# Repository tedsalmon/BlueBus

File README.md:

View this project on [CADLAB.io](https://cadlab.io/project/1479).

# BlueBus

BlueBus is a Bluetooth interface module for BMW vehicles equipped with the I-Bus. It emulates a CD changer on the I-Bus to provide seamless Bluetooth audio, hands-free telephony, and comfort feature integration while maintaining full compatibility with original vehicle systems.

## Supported Vehicles

BlueBus is compatible with BMW vehicles using the I-Bus architecture:

| Platform | Models | Years |
|----------|--------|-------|
| E38 | 7 Series | 1994-2001 |
| E39 | 5 Series | 1995-2004 |
| E46 | 3 Series | 1997-2006 |
| E52 | Z8 | 2000-2003 |
| E53 | X5 | 1999-2006 |
| E83 | X3 | 2003-2010 |
| E85 | Z4 | 2003-2008 |
| E86 | Z4 | 2005-2008 |
| R50/R52/R53 | MINI | 2000-2006 |

## Features

### Bluetooth Audio
* A2DP streaming with high-quality audio output over AAC
* AVRCP metadata display (artist, title, album) on vehicle screens
* Full playback control via vehicle buttons

### Hands-Free Telephony
* HFP (Hands-Free Profile) with factory microphone integration
* Caller ID display on vehicle screen
* Answer/end calls via vehicle controls
* Telephone LED control (Red = Device Disconnected, Green = Connected)
* Voice recognition support via Siri / Google Assistant
* Emulation of OE telephone system (Minus the Menus, for now)

### Vehicle Integration
* Native DSP compatibility (analog and S/PDIF inputs)
* On-Board Computer data display (coolant temp, ambient temp, oil temp)
* GPS time synchronization for vehicles with factory Nav
* Park Distance Control integration

### Comfort Features
* Auto-lock at configurable speed threshold
* Auto-unlock on ignition off
* Comfort turn signals (Tap to signal)
* Parking lamp control

### System
* Firmware upgradable via USB
* Multi-language support (9 languages)
* Up to 8 paired Bluetooth devices

## Supported Display Units

| Unit | Description | Display |
|------|-------------|---------|
| BMBT | Board Monitor (Navigation) | Full graphical menus |
| MID | Multi-Information Display | 24-character single line |
| CD53 | Business CD Radio | 11-character single line |
| MIR | Multi-Information Radio | Single line display |

## Hardware

### Core Components
| Component | Description |
|-----------|-------------|
| PIC24FJ1024GA606 | 16-bit MCU @ 16MHz, 1MB Flash |
| BM83 | Microchip Bluetooth 5.0 Module |
| Melexis TH3122.4 | I-Bus Transceiver |

### Audio Chain
| Component | Description |
|-----------|-------------|
| PCM5122 | Line-Level DAC, 2.1V RMS, 113 dB SNR |
| DIT4096 | S/PDIF Encoder |
| PAM8406 | 5W Class-D/Class-AB Amplifier |

### Interfaces
| Component | Description |
|-----------|-------------|
| FT231XS | USB to UART (firmware updates) |

## Configuration

Settings are stored in EEPROM and can be configured through the vehicle display menus. Categories include:

* **Audio** - DAC gain, DSP input source, volume offsets
* **Telephony** - HFP mode, microphone gain, volume
* **Comfort** - Auto-lock speed, blinker count, lighting options
* **UI** - Language, temperature units, display preferences
* **Navigation** - Auto-zoom, map display mode

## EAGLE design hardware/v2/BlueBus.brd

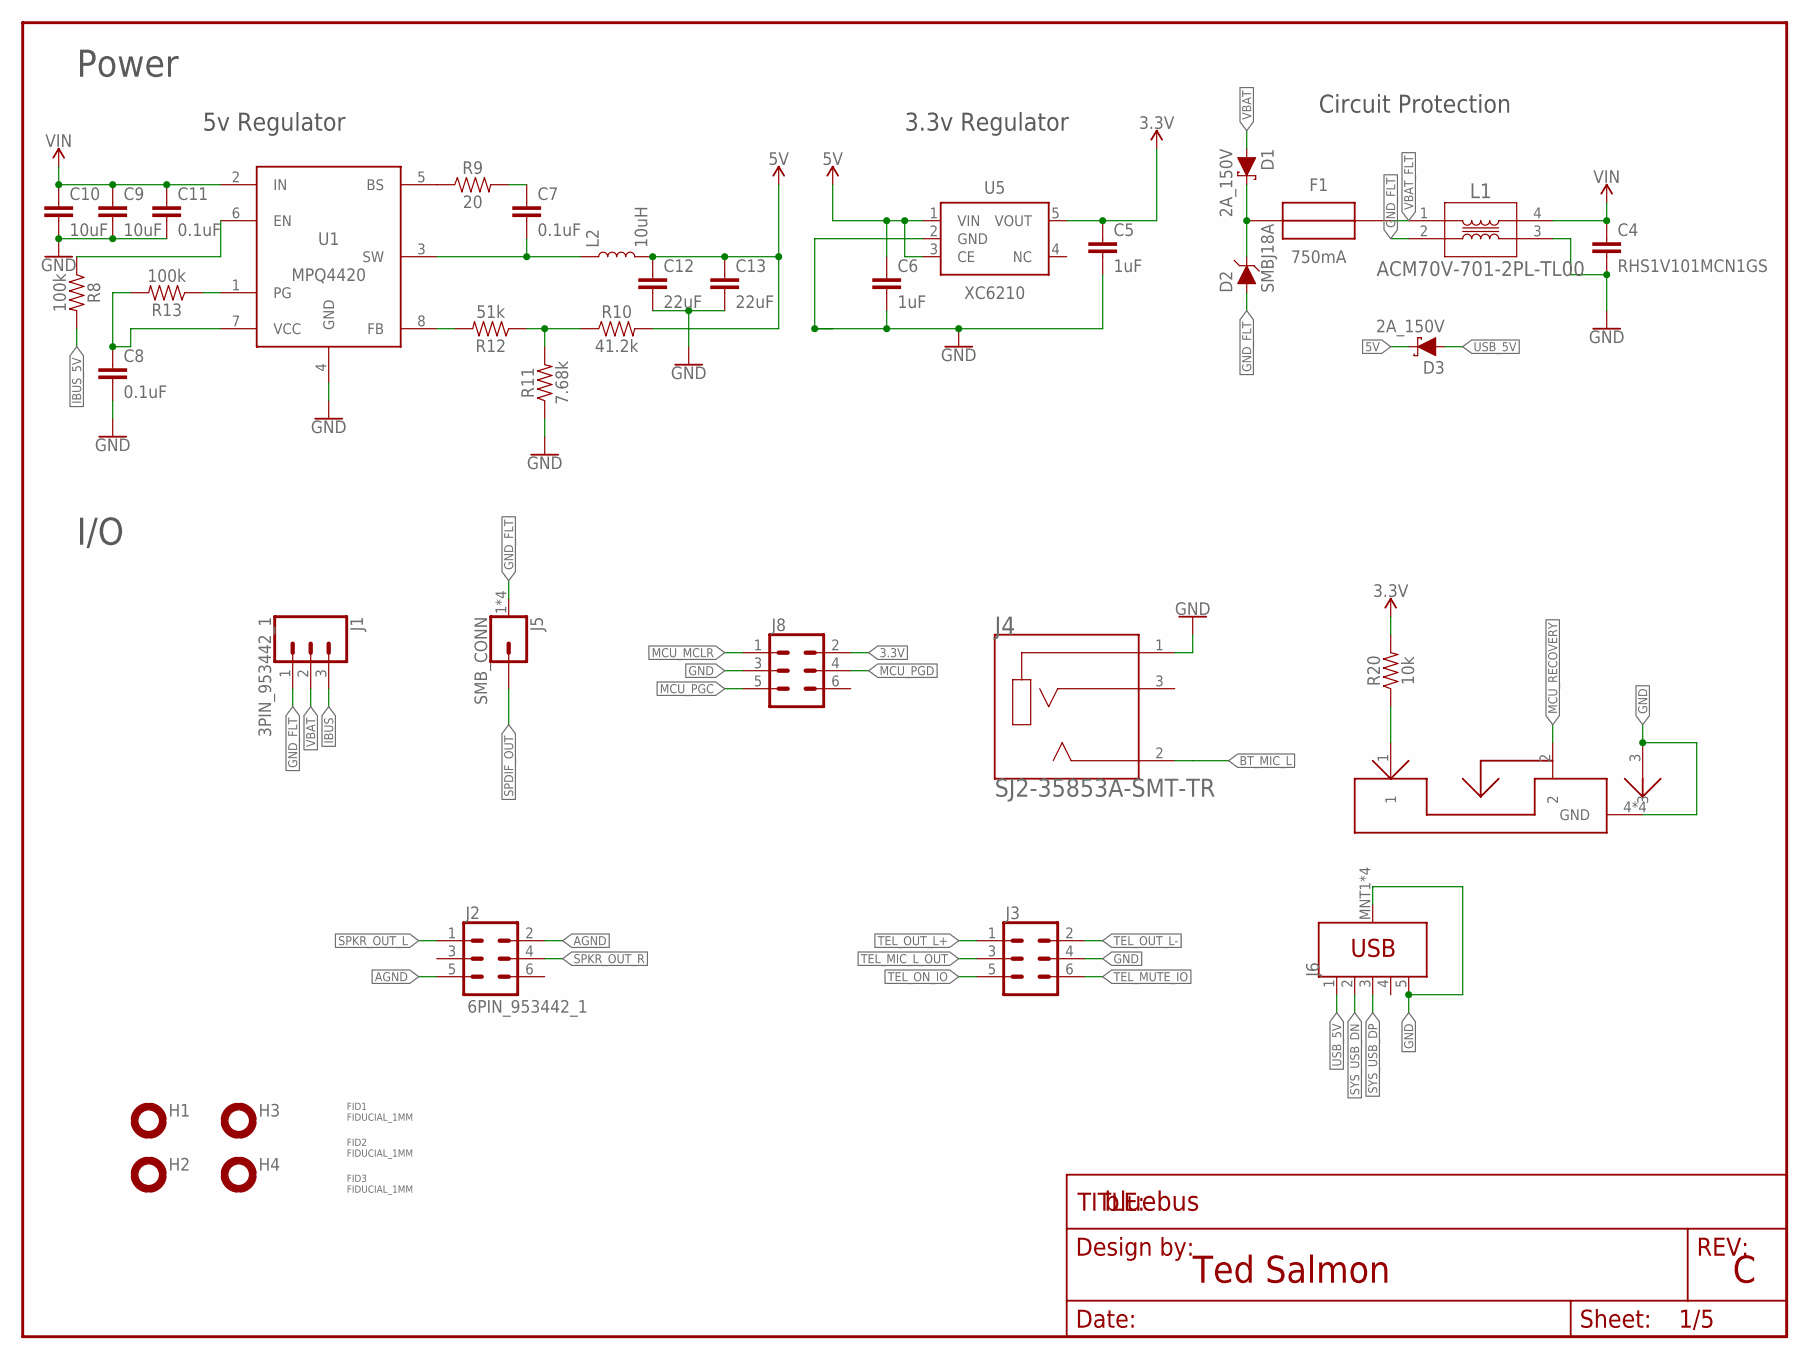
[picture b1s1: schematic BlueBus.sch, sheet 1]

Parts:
C4: RHS1V101MCN1GS
C5, C6: 1uF; 0603
C7, C8, C11: 0.1uF; 0603
C9, C10: 10uF; 1206
C12, C13: 22uF; 0805
D1, D3: 2A_150V; SOD123FL-2
D2: SMBJ18A; DO-214AA
F1: 750mA; LITTLEFUSE
FID1, FID2, FID3: FIDUCIAL_1MM
FRAME1: FRAME-LETTER; DUMMY
H1, H2, H3, H4: 2,5-HOLE; 2.5-HOLE
J1: 3PIN_953442_1; TE_MQS_3PIN
J2: 6PIN_953442_1; TE_MQS_6PIN
J3: 6PIN_5_103166_1; TE_AMPMODU_6_PIN
J4: SJ2-35853A-SMT-TR; CUI_SJ2_35853A_SMT_TR
J5: SMB_CONN; MOLEX_SMB
J6: USB3080-30-01-A
J7: PCM12SMTR
J8: TC2030NL; TC2030-NL
L1: ACM70V-701-2PL-TL00
L2: 10uH; MPL-SE5040
R8, R13: 100k; 0603
R9: 20; 0603
R10: 41.2k; 0603
R11: 7.68k; 0603
R12: 51k; 0603
R20: 10k; 0603
U1: MPQ4420; TSOT23-8
U5: XC6210; SOT23-5

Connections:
3.3V: C5.1, J8.2, R20.2, U5.5 (VOUT); also elsewhere on the board
5V: C6.1, C12.1, C13.1, D3.C, L2.2, R10.2, U5.1 (VIN), U5.3 (CE); also elsewhere on the board
5VREG_BS: R9.1, U1.5 (BS)
5VREG_BS_CAP: C7.1, R9.2
5VREG_EN: R8.1, U1.6 (EN)
5VREG_FB: R12.2, U1.8 (FB)
5VREG_FB_T: R10.1, R11.2, R12.1
5VREG_PG: R13.1, U1.1 (PG)
5VREG_SW: C7.2, L2.1, U1.3 (SW)
5VREG_VCC: C8.1, R13.2, U1.7 (VCC)
AGND: J2.2, J2.5; also elsewhere on the board
BT_MIC_L: J4.2 (TIP); also elsewhere on the board
GND: C4.2, C5.2, C6.2, C8.2, C9.2, C10.2, C11.2, C12.2, C13.2, J3.4, J4.1 (SLEEVE), J6.5 (GND), J6.MNT1 (SHIELD), J6.MNT2 (SHIELD), J6.MNT3 (SHIELD), J6.MNT4 (SHIELD), J7.3, J7.4 (GND), J7.5 (GND), J7.6 (GND), J7.7 (GND), J8.3, L1.3, R11.1, U1.4 (GND), U5.2 (GND); also elsewhere on the board
GND_FLT: D2.A, J1.1, J5.1 (GND), J5.2 (GND), J5.3 (GND), J5.4 (GND), L1.2
IBUS: J1.3; also elsewhere on the board
IBUS_5V: R8.2; also elsewhere on the board
MCU_MCLR: J8.1; also elsewhere on the board
MCU_PGC: J8.5; also elsewhere on the board
MCU_PGD: J8.4; also elsewhere on the board
MCU_RECOVERY: J7.2; also elsewhere on the board
RECOVERY_ON: J7.1, R20.1
SPDIF_OUT: J5.P$1 (1); also elsewhere on the board
SPKR_OUT_L: J2.1; also elsewhere on the board
SPKR_OUT_R: J2.4; also elsewhere on the board
SYS_USB_DN: J6.2 (D-); also elsewhere on the board
SYS_USB_DP: J6.3 (D+); also elsewhere on the board
TEL_MIC_L_OUT: J3.3; also elsewhere on the board
TEL_MUTE_IO: J3.6; also elsewhere on the board
TEL_ON_IO: J3.5; also elsewhere on the board
TEL_OUT_L+: J3.1; also elsewhere on the board
TEL_OUT_L-: J3.2; also elsewhere on the board
USB_5V: D3.A, J6.1 (VBUS)
VBAT: D1.A, J1.2
VBAT_DIODE: D1.C, D2.C, F1.IN (OUT)
VBAT_FLT: F1.OUT (IN), L1.1
VIN: C4.1, C9.1, C10.1, C11.1, L1.4, U1.2 (IN); also elsewhere on the board

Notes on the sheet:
Ted Salmon
Power
I/O
3.3v Regulator
5v Regulator
Circuit Protection

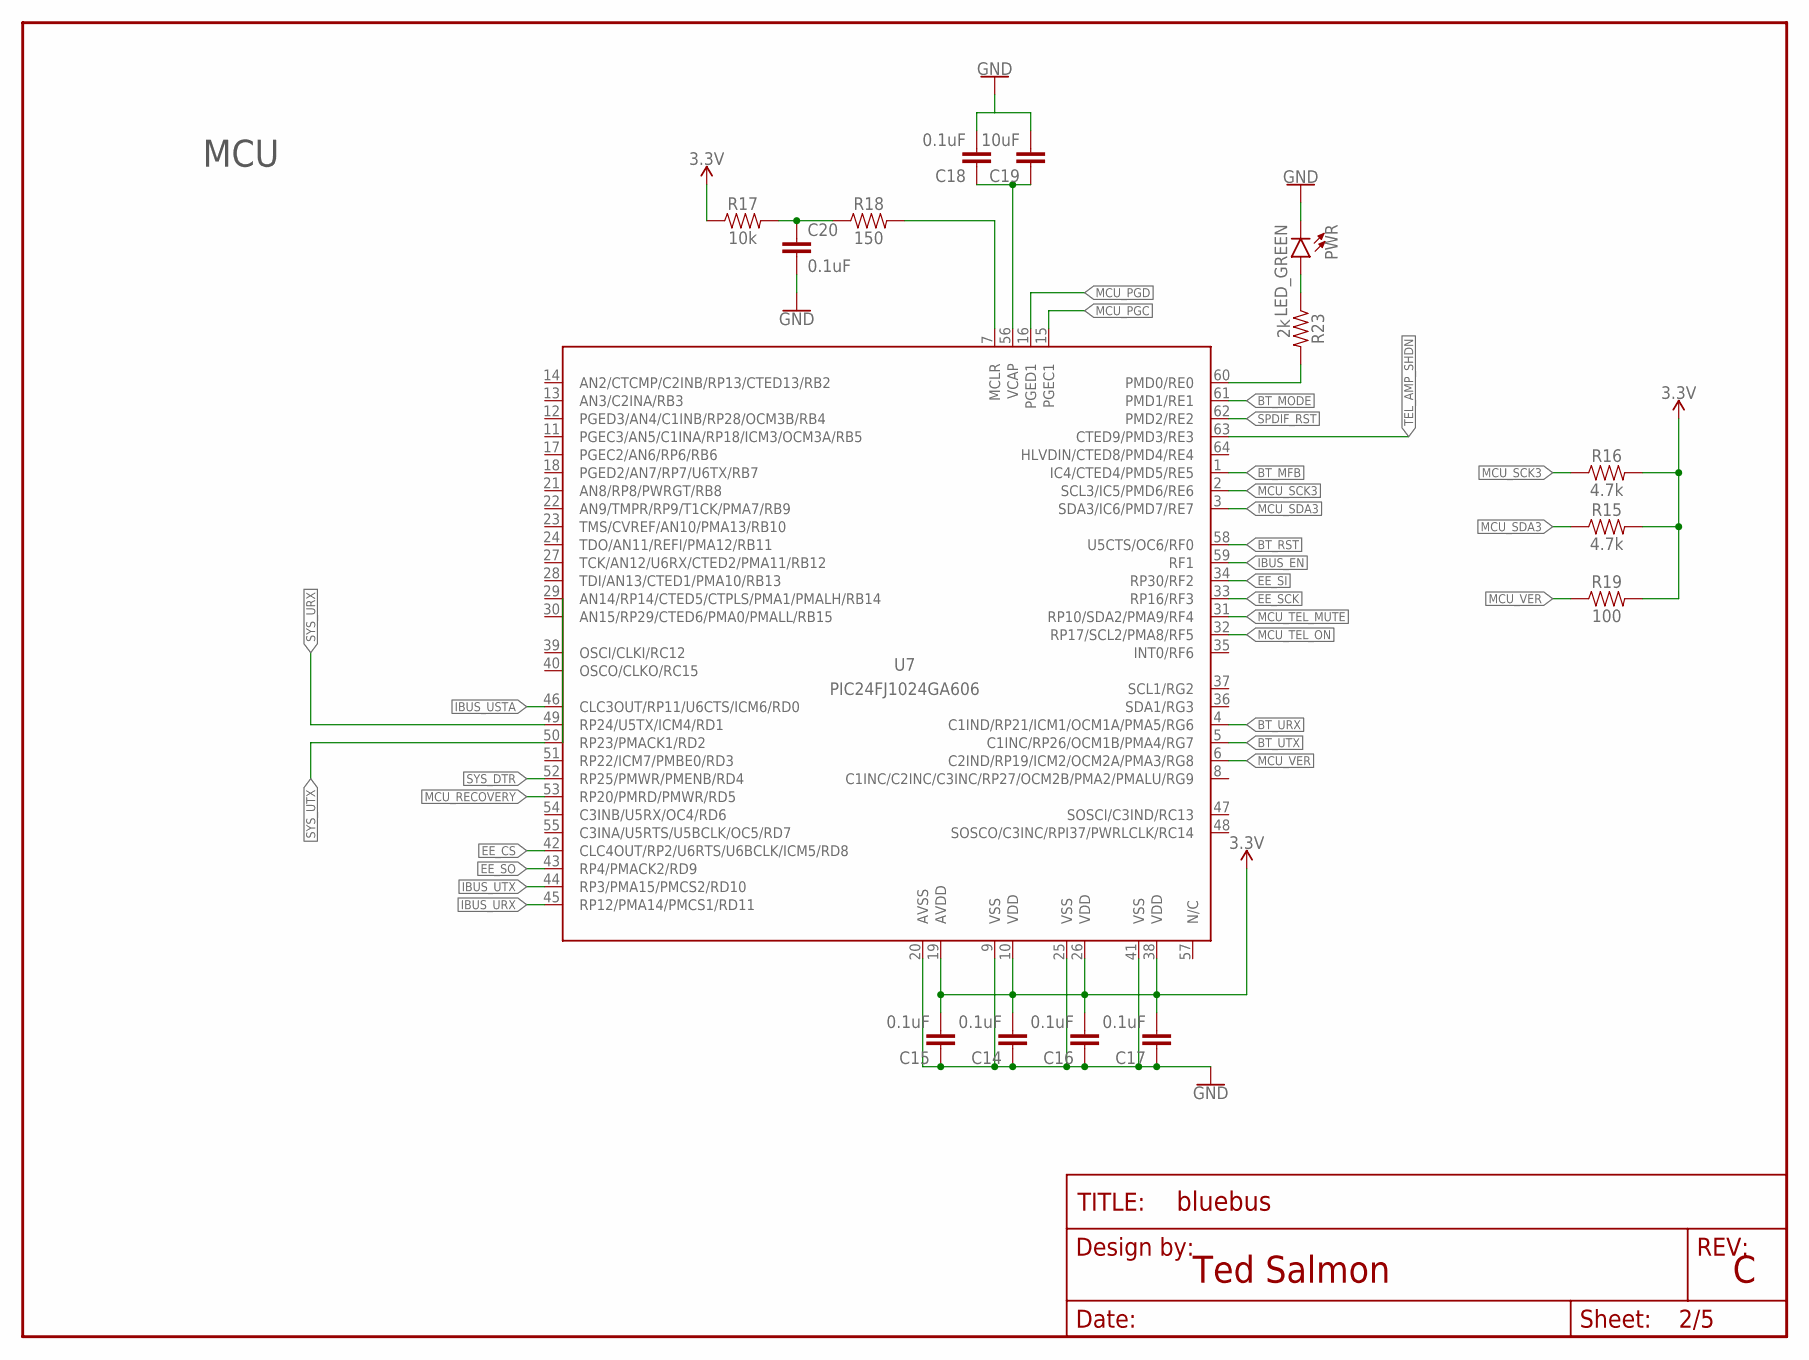
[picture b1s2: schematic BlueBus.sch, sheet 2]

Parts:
C14, C15, C16, C17, C18, C20: 0.1uF; 0603
C19: 10uF; 0603
FRAME2: FRAME-LETTER; DUMMY
PWR: LED_GREEN; LED-0805
R15, R16: 4.7k; 0603
R17: 10k; 0603
R18: 150; 0603
R19: 100; 0603
R23: 2k; 0603
U7: PIC24FJ1024GA606; TQFP64

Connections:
3.3V: C14.2, C15.2, C16.2, C17.2, R15.2, R16.2, R17.1, R19.2, U7.10 (VDD), U7.19 (AVDD), U7.26 (VDD), U7.38 (VDD); also elsewhere on the board
BT_MFB: U7.1 (IC4/CTED4/PMD5/RE5); also elsewhere on the board
BT_MODE: U7.61 (PMD1/RE1); also elsewhere on the board
BT_RST: U7.58 (U5CTS/OC6/RF0); also elsewhere on the board
BT_URX: U7.4 (C1IND/RP21/ICM1/OCM1A/PMA5/RG6); also elsewhere on the board
BT_UTX: U7.5 (C1INC/RP26/OCM1B/PMA4/RG7); also elsewhere on the board
EE_CS: U7.42 (CLC4OUT/RP2/U6RTS/U6BCLK/ICM5/RD8); also elsewhere on the board
EE_SCK: U7.33 (RP16/RF3); also elsewhere on the board
EE_SI: U7.34 (RP30/RF2); also elsewhere on the board
EE_SO: U7.43 (RP4/PMACK2/RD9); also elsewhere on the board
GND: C14.1, C15.1, C16.1, C17.1, C18.2, C19.2, C20.2, PWR.- (C), U7.9 (VSS), U7.20 (AVSS), U7.25 (VSS), U7.41 (VSS); also elsewhere on the board
IBUS_EN: U7.59 (RF1); also elsewhere on the board
IBUS_URX: U7.45 (RP12/PMA14/PMCS1/RD11); also elsewhere on the board
IBUS_USTA: U7.46 (CLC3OUT/RP11/U6CTS/ICM6/RD0); also elsewhere on the board
IBUS_UTX: U7.44 (RP3/PMA15/PMCS2/RD10); also elsewhere on the board
MCU_MCLR: R18.2, U7.7 (MCLR); also elsewhere on the board
MCU_MCLR_RES: C20.1, R17.2, R18.1
MCU_ON_LED: R23.2, U7.60 (PMD0/RE0)
MCU_ON_LED_RES: PWR.+ (A), R23.1
MCU_PGC: U7.15 (PGEC1); also elsewhere on the board
MCU_PGD: U7.16 (PGED1); also elsewhere on the board
MCU_RECOVERY: U7.53 (RP20/PMRD/PMWR/RD5); also elsewhere on the board
MCU_SCK3: R16.1, U7.2 (SCL3/IC5/PMD6/RE6); also elsewhere on the board
MCU_SDA3: R15.1, U7.3 (SDA3/IC6/PMD7/RE7); also elsewhere on the board
MCU_TEL_MUTE: U7.31 (RP10/SDA2/PMA9/RF4); also elsewhere on the board
MCU_TEL_ON: U7.32 (RP17/SCL2/PMA8/RF5); also elsewhere on the board
MCU_VCAP: C18.1, C19.1, U7.56 (VCAP)
MCU_VER: R19.1, U7.6 (C2IND/RP19/ICM2/OCM2A/PMA3/RG8)
SPDIF_RST: U7.62 (PMD2/RE2); also elsewhere on the board
SYS_DTR: U7.52 (RP25/PMWR/PMENB/RD4); also elsewhere on the board
SYS_URX: U7.49 (RP24/U5TX/ICM4/RD1); also elsewhere on the board
SYS_UTX: U7.50 (RP23/PMACK1/RD2); also elsewhere on the board
TEL_AMP_SHDN: U7.63 (CTED9/PMD3/RE3); also elsewhere on the board

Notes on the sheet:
Ted Salmon
MCU

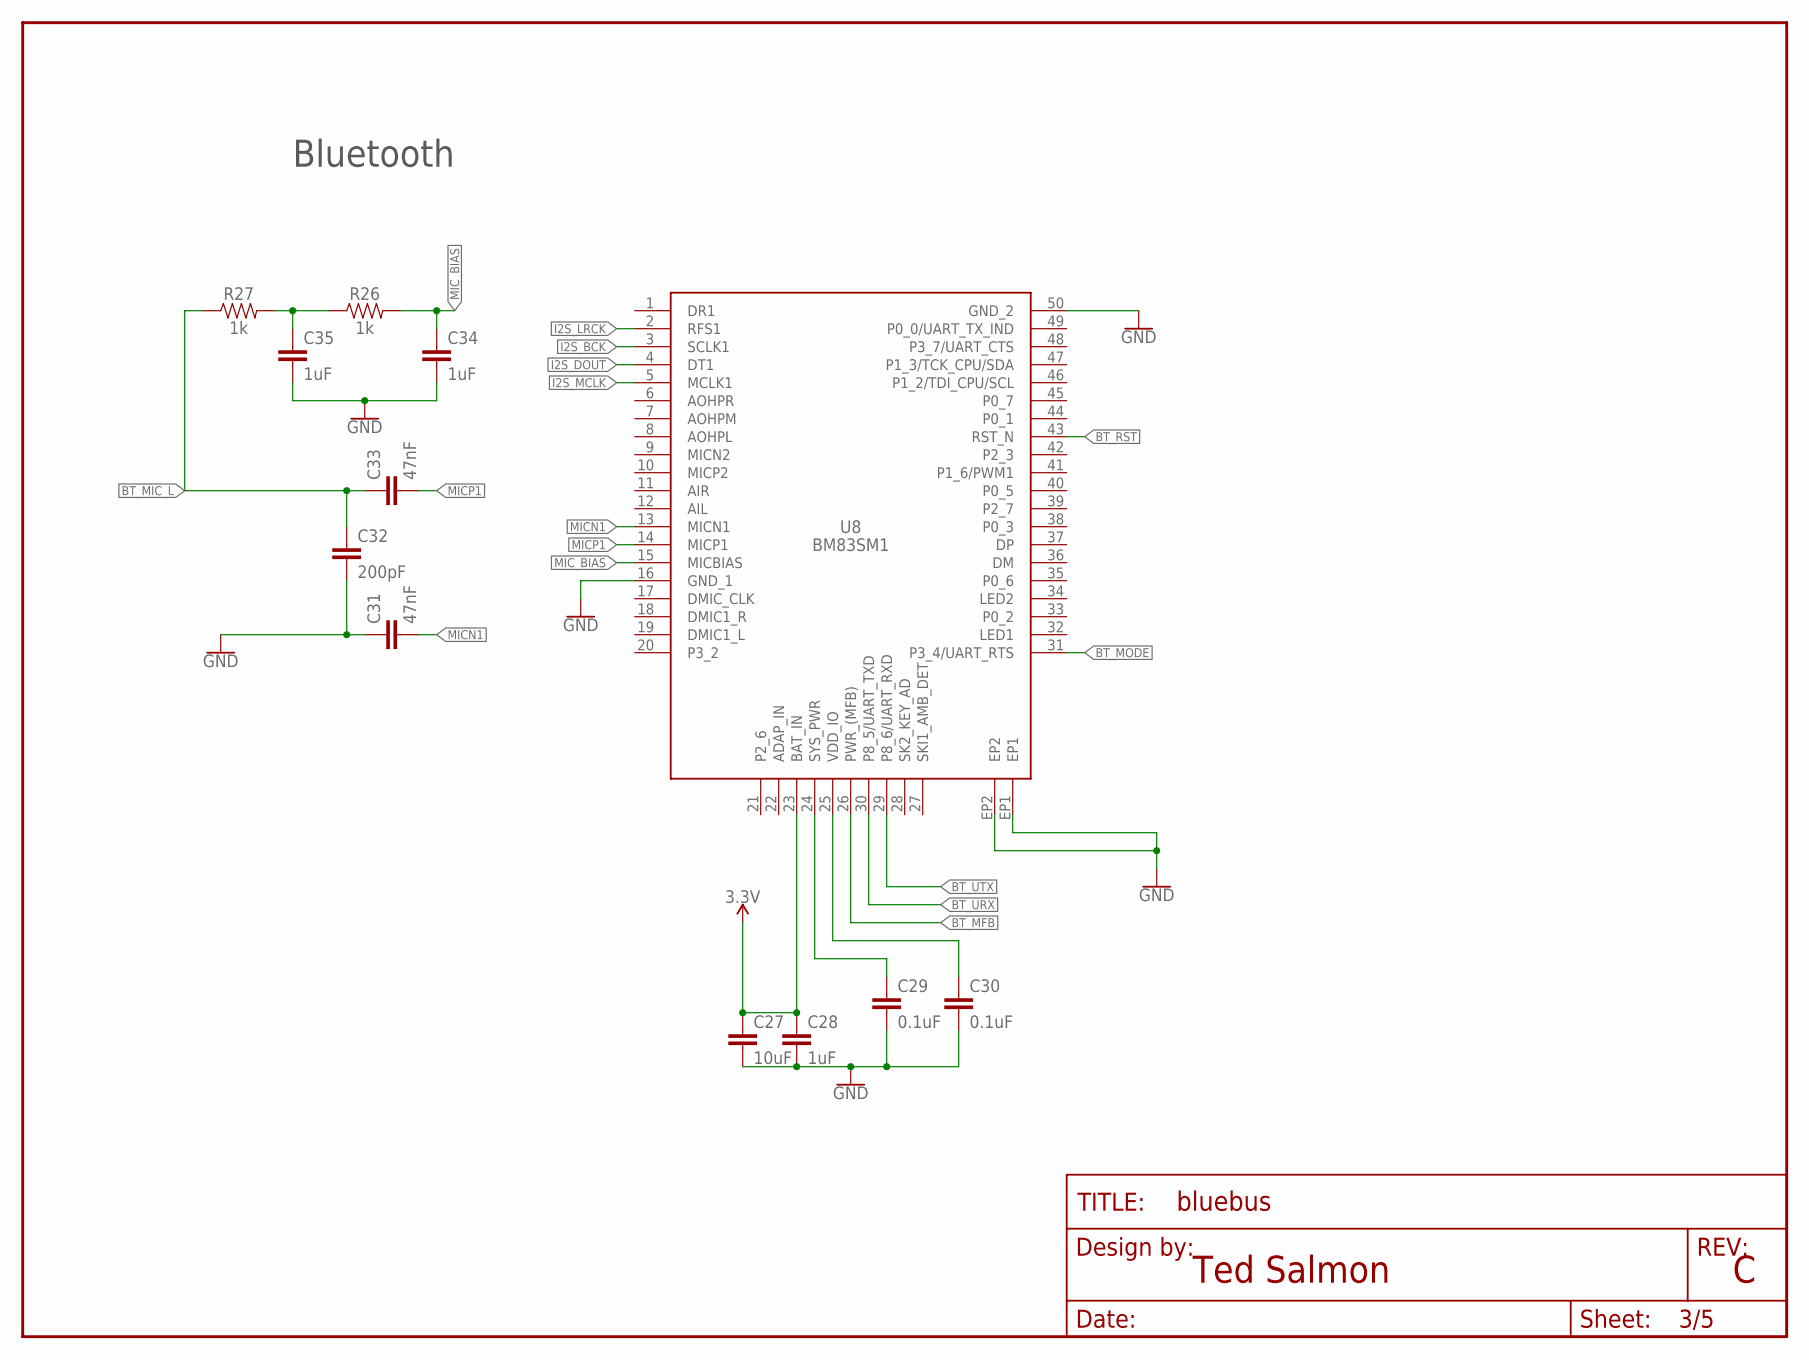
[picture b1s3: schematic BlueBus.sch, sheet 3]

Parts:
C27: 10uF; 0603
C28, C34, C35: 1uF; 0603
C29, C30: 0.1uF; 0603
C31, C33: 47nF; 0603
C32: 200pF; 0603
FRAME4: FRAME-LETTER; DUMMY
R26, R27: 1k; 0603
U8: BM83SM1

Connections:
3.3V: C27.1, C28.1, U8.23 (BAT_IN); also elsewhere on the board
BT_MFB: U8.26 (PWR_(MFB)); also elsewhere on the board
BT_MIC_L: C32.1, C33.1, R27.1; also elsewhere on the board
BT_MODE: U8.31 (P3_4/UART_RTS); also elsewhere on the board
BT_RST: U8.43 (RST_N); also elsewhere on the board
BT_SYS_PWR: C29.1, U8.24 (SYS_PWR)
BT_URX: U8.30 (P8_5/UART_TXD); also elsewhere on the board
BT_UTX: U8.29 (P8_6/UART_RXD); also elsewhere on the board
BT_VDD_IO: C30.1, U8.25 (VDD_IO)
GND: C27.2, C28.2, C29.2, C30.2, C31.1, C32.2, C34.2, C35.2, U8.16 (GND_1), U8.50 (GND_2), U8.EP1, U8.EP2; also elsewhere on the board
I2S_BCK: U8.3 (SCLK1); also elsewhere on the board
I2S_DOUT: U8.4 (DT1); also elsewhere on the board
I2S_LRCK: U8.2 (RFS1); also elsewhere on the board
I2S_MCLK: U8.5 (MCLK1); also elsewhere on the board
MICN1: C31.2, U8.13 (MICN1)
MICP1: C33.2, U8.14 (MICP1)
MICP1_RES: C35.1, R26.1, R27.2
MIC_BIAS: C34.1, R26.2, U8.15 (MICBIAS)

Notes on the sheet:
Bluetooth
Ted Salmon

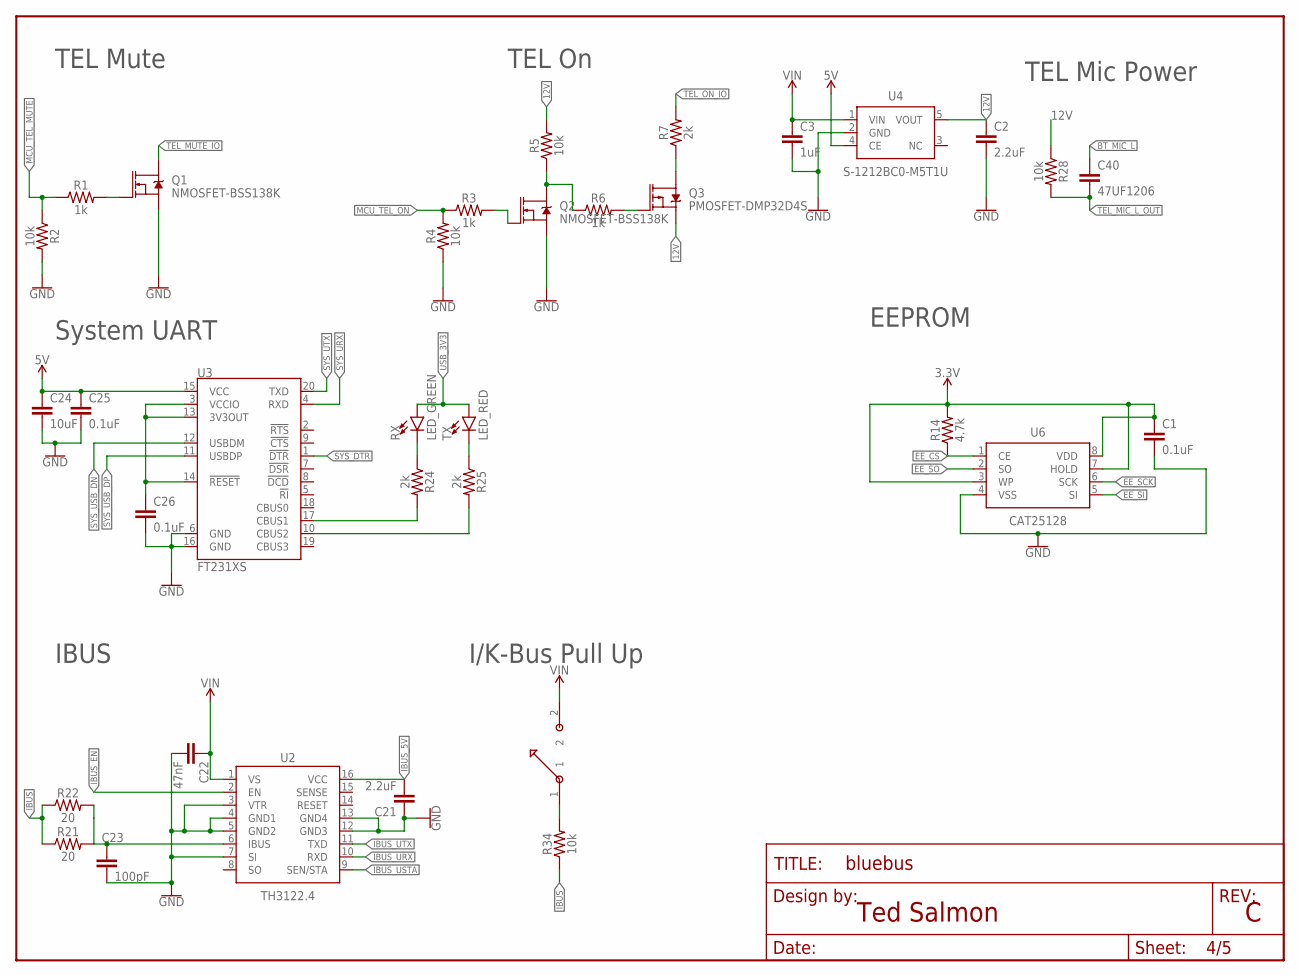
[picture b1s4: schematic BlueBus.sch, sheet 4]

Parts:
C1, C25, C26: 0.1uF; 0603
C2, C21: 2.2uF; 0603
C3: 1uF; 0603
C22: 47nF; 0603
C23: 100pF; 0603
C24: 10uF; 0603
C40: 47UF1206; 1206
FRAME3: FRAME-LETTER; DUMMY
Q1, Q2: NMOSFET-BSS138K; SOT-23
Q3: PMOSFET-DMP32D4S; SOT-23
R1, R3, R6: 1k; 0603
R2, R4, R5, R28, R34: 10k; 0603
R7, R24, R25: 2k; 0603
R14: 4.7k; 0603
R21, R22: 20; 0603
RX: LED_GREEN; LED-0805
SW1: CHS-01TA1
TX: LED_RED; LED-0805
U2: TH3122.4; SOIC16DF
U3: FT231XS; SSOP20_L
U4: S-1212BC0-M5T1U; SOT23-5
U6: CAT25128; TSSOP-8

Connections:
3.3V: C1.1, R14.2, U6.3 (WP), U6.7 (HOLD), U6.8 (VDD); also elsewhere on the board
5V: C24.1, C25.1, U3.15 (VCC), U4.4 (CE); also elsewhere on the board
12V: C2.1, Q3.2 (S), R5.2, R28.1, U4.5 (VOUT)
BT_MIC_L: C40.1; also elsewhere on the board
EE_CS: R14.1, U6.1 (CE); also elsewhere on the board
EE_SCK: U6.6 (SCK); also elsewhere on the board
EE_SI: U6.5 (SI); also elsewhere on the board
EE_SO: U6.2 (SO); also elsewhere on the board
GND: C1.2, C2.2, C3.2, C21.1, C22.2, C23.2, C24.2, C25.2, C26.2, Q1.2 (S), Q2.2 (S), R2.2, R4.1, U2.3 (VTR), U2.4 (GND1), U2.5 (GND2), U2.7 (SI), U2.12 (GND3), U2.13 (GND4), U3.6 (GND), U3.16 (GND), U4.2 (GND), U6.4 (VSS); also elsewhere on the board
IBUS: R21.1, R22.1, R34.1; also elsewhere on the board
IBUS_5V: C21.2, U2.16 (VCC); also elsewhere on the board
IBUS_EN: U2.2 (EN); also elsewhere on the board
IBUS_FILT: C23.1, R21.2, R22.2, U2.6 (IBUS)
IBUS_PU: R34.2, SW1.1
IBUS_URX: U2.10 (RXD); also elsewhere on the board
IBUS_USTA: U2.9 (SEN/STA); also elsewhere on the board
IBUS_UTX: U2.11 (TXD); also elsewhere on the board
MCU_TEL_MUTE: R1.1, R2.1; also elsewhere on the board
MCU_TEL_MUTE_RES: Q1.1 (G), R1.2
MCU_TEL_ON: R3.1, R4.2; also elsewhere on the board
MCU_TEL_ON_NRES: Q2.1 (G), R3.2
SYS_DTR: U3.1 (!DTR); also elsewhere on the board
SYS_RX_LED: R24.2, U3.17 (CBUS1)
SYS_RX_LED_RES: R24.1, RX.- (C)
SYS_TX_LED: R25.2, U3.10 (CBUS2)
SYS_TX_LED_RES: R25.1, TX.- (C)
SYS_URX: U3.4 (RXD); also elsewhere on the board
SYS_USB_DN: U3.12 (USBDM); also elsewhere on the board
SYS_USB_DP: U3.11 (USBDP); also elsewhere on the board
SYS_UTX: U3.20 (TXD); also elsewhere on the board
TEL_MIC_L_OUT: C40.2, R28.2; also elsewhere on the board
TEL_MUTE_IO: Q1.3 (D); also elsewhere on the board
TEL_ON: Q3.3 (D), R7.1
TEL_ON_IO: R7.2; also elsewhere on the board
TEL_ON_P: Q2.3 (D), R5.1, R6.1
TEL_ON_P_RES: Q3.1 (G), R6.2
USB_3V3: C26.1, RX.+ (A), TX.+ (A), U3.3 (VCCIO), U3.13 (3V3OUT), U3.14 (!RESET)
VIN: C3.1, C22.1, SW1.2, U2.1 (VS), U4.1 (VIN); also elsewhere on the board

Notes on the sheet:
Ted Salmon
IBUS
EEPROM
TEL On
TEL Mute
TEL Mic Power
System UART
I/K-Bus Pull Up

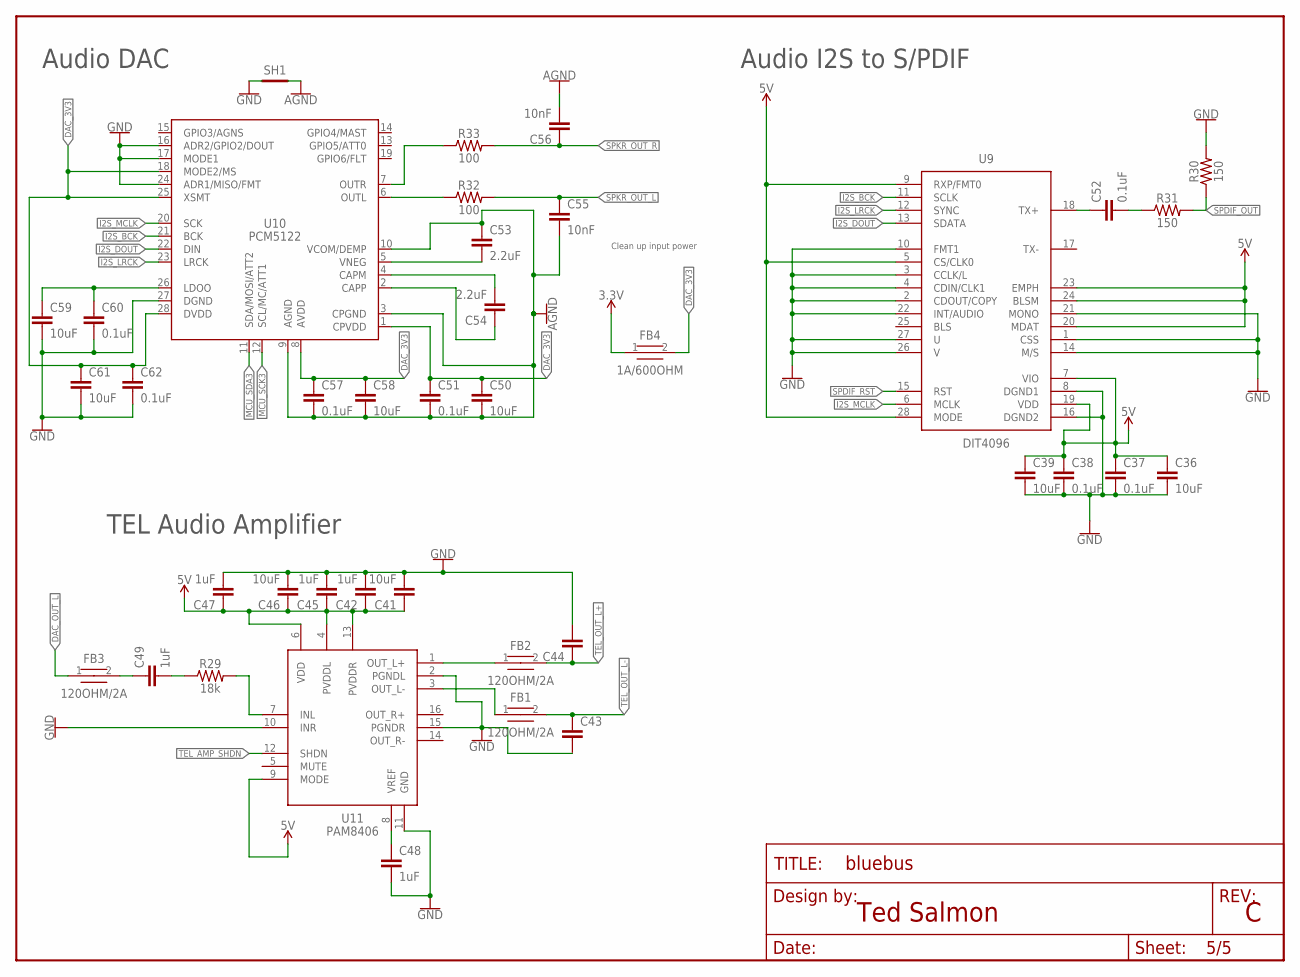
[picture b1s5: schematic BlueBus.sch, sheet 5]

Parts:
C36, C39, C41, C46, C50, C58, C59, C61: 10uF; 0603
C37, C38, C51, C52, C57, C60, C62: 0.1uF; 0603
C42, C45, C47, C48, C49: 1uF; 0603
C43, C44: 200pF; 0603
C53, C54: 2.2uF; 0603
C55, C56: 10nF; 0603
FB1, FB2, FB3: 120OHM/2A; 0603
FB4: 1A/600OHM; 0603
FRAME5: FRAME-LETTER; DUMMY
R29: 18k; 0603
R30, R31: 150; 0603
R32, R33: 100; 0603
SH1: SHORTT5; SHORT_TOP-50
U9: DIT4096; TSSOP28
U10: PCM5122; TSSOP28
U11: PAM8406; SOP-16

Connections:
3.3V: FB4.1; also elsewhere on the board
5V: C36.1, C37.1, C38.1, C39.1, C41.1, C42.1, C45.1, C46.1, C47.1, U9.5 (CS/CLK0), U9.7 (VIO), U9.9 (RXP/FMT0), U9.19 (VDD), U9.20 (MDAT), U9.23 (EMPH), U9.24 (BLSM), U9.28 (MODE), U11.4 (PVDDL), U11.6 (VDD), U11.9 (MODE), U11.13 (PVDDR); also elsewhere on the board
AGND: C50.2, C51.2, C53.1, C55.2, C56.2, C57.2, C58.2, SH1.2, U10.3 (CPGND), U10.9 (AGND), U10.10 (VCOM/DEMP); also elsewhere on the board
DAC_3V3: C50.1, C51.1, C57.1, C58.1, C61.1, C62.1, FB4.2, U10.1 (CPVDD), U10.8 (AVDD), U10.18 (MODE2/MS), U10.25 (XSMT), U10.28 (DVDD)
DAC_CAPM: C54.2, U10.4 (CAPM)
DAC_CAPP: C54.1, U10.2 (CAPP)
DAC_LDOO: C59.1, C60.1, U10.26 (LDOO)
DAC_OUT_L: FB3.1, R32.1, U10.6 (OUTL)
DAC_OUT_R: R33.1, U10.7 (OUTR)
DAC_VNEG: C53.2, U10.5 (VNEG)
GND: C36.2, C37.2, C38.2, C39.2, C41.2, C42.2, C43.2, C44.2, C45.2, C46.2, C47.2, C48.2, C59.2, C60.2, C61.2, C62.2, R30.2, SH1.1, U9.1 (CSS), U9.2 (CDOUT/COPY), U9.3 (CCLK/L), U9.4 (CDIN/CLK1), U9.8 (DGND1), U9.10 (FMT1), U9.14 (M/S), U9.16 (DGND2), U9.21 (MONO), U9.22 (INT/AUDIO), U9.26 (V), U9.27 (U), U10.16 (ADR2/GPIO2/DOUT), U10.17 (MODE1), U10.24 (ADR1/MISO/FMT), U10.27 (DGND), U11.2 (PGNDL), U11.10 (INR), U11.11 (GND), U11.15 (PGNDR); also elsewhere on the board
I2S_BCK: U9.11 (SCLK), U10.21 (BCK); also elsewhere on the board
I2S_DOUT: U9.13 (SDATA), U10.22 (DIN); also elsewhere on the board
I2S_LRCK: U9.12 (SYNC), U10.23 (LRCK); also elsewhere on the board
I2S_MCLK: U9.6 (MCLK), U10.20 (SCK); also elsewhere on the board
MCU_SCK3: U10.12 (SCL/MC/ATT1); also elsewhere on the board
MCU_SDA3: U10.11 (SDA/MOSI/ATT2); also elsewhere on the board
SPDIF_OUT: R30.1, R31.2; also elsewhere on the board
SPDIF_RST: U9.15 (RST); also elsewhere on the board
SPDIF_TX_FLT: C52.1, U9.18 (TX+)
SPDIF_TX_RES: C52.2, R31.1
SPKR_OUT_L: C55.1, R32.2; also elsewhere on the board
SPKR_OUT_R: C56.1, R33.2; also elsewhere on the board
TEL_AMP_IN: C49.1, FB3.2
TEL_AMP_INL: R29.2, U11.7 (INL)
TEL_AMP_INL_CAP_RES: C49.2, R29.1
TEL_AMP_OUT_L+: FB2.1, U11.1 (OUT_L+)
TEL_AMP_OUT_L-: FB1.1, U11.3 (OUT_L-)
TEL_AMP_SHDN: U11.12 (SHDN); also elsewhere on the board
TEL_AMP_VREF: C48.1, U11.8 (VREF)
TEL_OUT_L+: C44.1, FB2.2; also elsewhere on the board
TEL_OUT_L-: C43.1, FB1.2; also elsewhere on the board

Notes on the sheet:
Audio DAC
Audio I2S to S/PDIF
TEL Audio Amplifier
Ted Salmon
Clean up input power

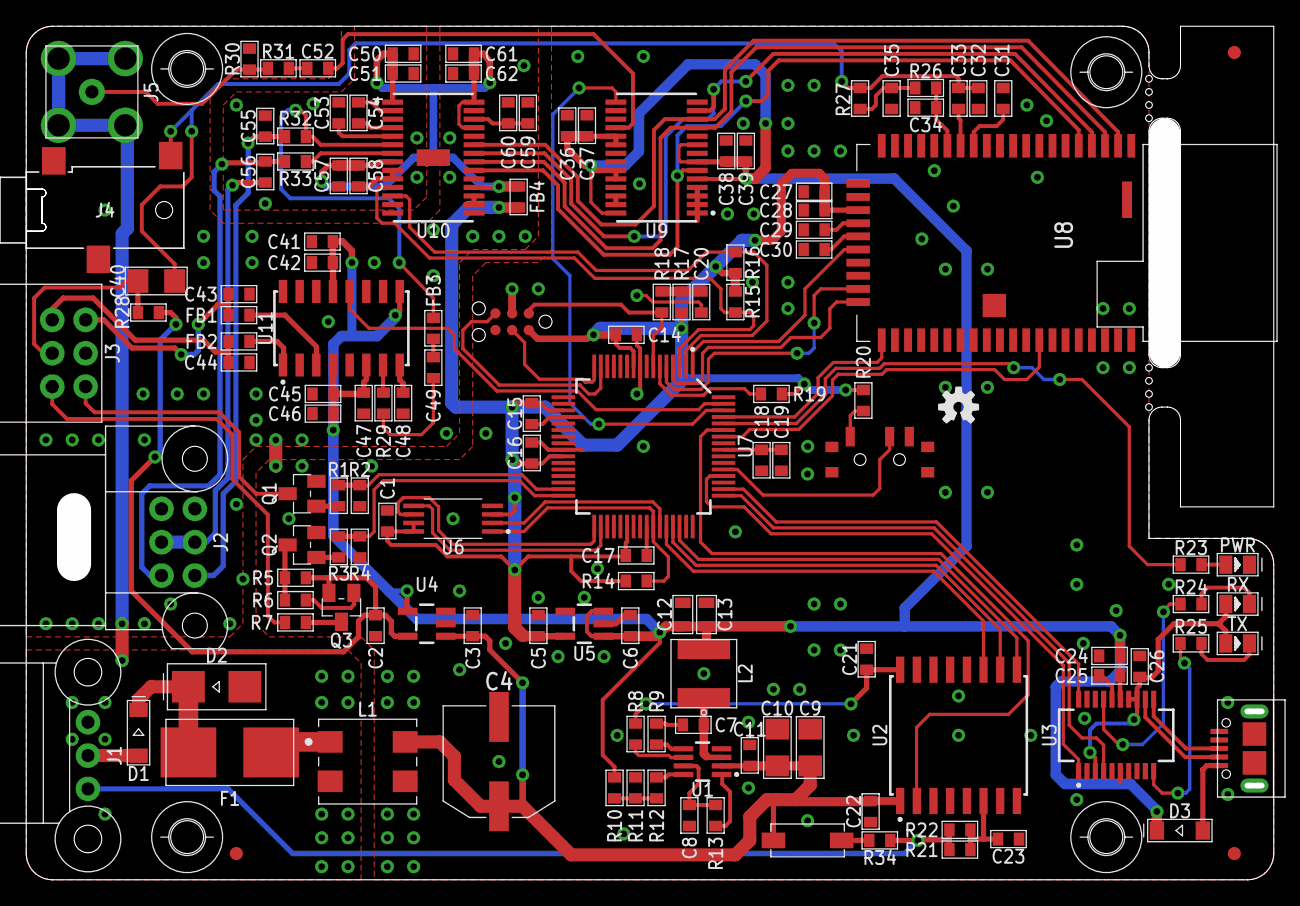
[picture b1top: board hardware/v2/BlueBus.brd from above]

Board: 2 copper layers, 95.0 x 65.0 mm, 146 parts (0 on the bottom side), 101 nets.

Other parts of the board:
U$1: OSHW-LOGO-S

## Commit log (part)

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2023-01-05 Add utility functions.
2023-01-06 [FIX] firmware: 1.3.1 / 1.3.2 Styling changes
2023-01-08 Add LCM_BROADCAST_INDICATORS_RESP processing.
2023-01-13 Workaround for iPhone not adhering to GSM 07.07 - AT Commands standards.
2023-01-15 [IMP] firmware: Application 1.3.2 * Update to toolchain 2.0.0 * Prevent RPOR (Reprogrammable pin) memory overflow by not reading registers above 15 * Prevent memory overflow caused by writing more ti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
2023-02-06 Add detailed logging around volume changes when calling.
2023-02-07 Cleanup logging
2023-02-07 TEL volume can also be lowered relative to music.
2023-02-08 Bluebus IBUS Function rename
2023-02-09 [IMP] firmware: Application 1.3.2 * Add code to turn BMBT back on any time that a button is pressed on the unit
2023-02-16 Fix occasional playback status desync
    Sync Playback Status with AVRCP periodically on BC127 to avoid missed messages or out of order commands messing the stored state.
    Store intended playback status when sending command, without wait for response from BT.
2023-02-20 When preferred Device MacID is stored, do not connect to other paired devices. Should select from Device Menu to pick new preferred device. TODO: could probably ignore preferred after some time of no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
2023-02-20 Clarify logging. Only initiate device when space in Device Table (should be always anyways).
2023-02-20 Update the build toolchain. Disable debug symbol generation.
2023-02-20 Store last connected device in EEPROM. Store selected device from menu in EEPROM. Reset Last MacID on pairing clear.
2023-02-20 Fix wrong reporting of PAUSED status.
2023-02-28 Display "Call" as caller-id on incoming call so there is clear differentiator when it is Voice Assistant talking or new call incoming. Fix Incoming constants typo.
2023-03-06 Honor the configuration.
2023-03-10 Add IKE numeric display command
2023-03-17 Reorganize display code, validate PDC response.
2023-03-21 Support PDC display configuration on single line UIs, do not offer RADIO/BMBT display yet.
2023-04-07 [IMP] firmware: Application Updates * Resolve issue with MID UI and spamming button press when clicking "MODE" * Resolve issues displaying DSP option on MID
2023-04-07 [ADD] utility: Log Praser Utility
    * Parse BlueBus session terminal logs for I-Bus messages and translate them into readable form.
    * Initial Data Parser framework
2023-04-08 Tidy Settings Display Code
2023-04-08 Update screen on changing HFP setting.
2023-04-08 Process Time from GPS, consolidate time update handlers.
2023-04-08 Configuration helpers for Time Zone and DST settings.
2023-04-08 Fix typo
2023-04-09 Updated localizations and No Signal info
2023-04-12 Trigger on reverse gear.
2023-04-28 [IMP] firmware: Application 1.3.3 * Auto Zoom Code Cleanup
2023-05-11 Remove Polish diacritic chars
    Latin-1 table unfortunately does not support most of Polish diacritic chars.
2023-05-13 Changed the "LOCALE_STRING_DASHBOARD" translation
2023-05-15 Fix version number
2023-06-17 Workaround for BC127 audio buffer not cleared on NEXT/PREV song (blip of old song played before new one starts).
2023-07-09 Generated config update
2023-07-09 Increase version to 1.4.0
2023-07-09 Add most recent strings to Polish localization.
2023-08-30 [IMP] firmware: Application 1.3.3 * Update Debug Verbiage
2023-10-12 [IMP] firmware: Application 1.3.3 * Minor line ending and whitespace changes
2023-11-24 [IMP] firmware: Application 1.3.4 * Prevent BT Call handling code from being hit if HFP is off * Default to Handsfree mode of NONE * Upgrade to 1.3.4
2023-11-24 [IMP] firmware: Application 1.3.4 * Report CD 1 for GT UI again
2023-11-24 [IMP] firmware: Application 1.3.4 [VM / GT] * Implement VM UI Auto configuration * Improve UI update protocol for older UI to resolve GT crashes
2023-11-24 [IMP] firmware: Application 1.3.4 * Ensure that DSP input mode is correctly tracked and set based on the selected setting
2023-12-31 Change to a limit of 16 characters maximum per translation
2024-01-02 Added one new string
2024-01-02 Fix implementation declaration in sync with header file
2024-02-11 Micro style update
2024-02-11 Fix LANG ids >= 0x10
2024-02-25 First build of PBAP phone book features for BM83. Includes phone dialer menu from feature/phone branch - but does not include directory menus. Phone book can be tested using CLI only ... "BT PB" (pho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
2024-03-06 Fix a typo
2024-03-08 Buffer overflows
2024-03-08 Redeclaration of volume in branches
2024-03-08 Add missing va_end
2024-03-08 Initialize all fields for new paired device.
2024-03-19 [IMP] firmware: Application buffer overflow fixes
    * Add missing va_end
    * Fix redundant OR with 0
    * Fix potential buffer overrun and have automatic cache size calculation
    * Initialize all fields for new paired device.
    * Fix a fix of SETTINGS CACHE
2024-03-19 [IMP] firmware: Application 1.3.4 * Mini Cooper R5x Improvements * Toggle the Nav UI via random play mode rather than just pinning it * Do NOT address the radio from the Navi if the car is an R5x but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
2024-03-19 [FIX] firmware: Application display glitches
    * After disabling of Dashboard Temps, the previous values remain on screen forever after commit
    Old MK does the cleanup anyway when rendering the Music details, filling \0x06 automatically, but for MKIV_STATIC it seems to need cleanup and it did not crash anyway, so seems oayk to be called ever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
    * Fix string trimming that breaks the display menu items clearing.
2024-03-22 Small cleanups
2024-03-22 Incorrect handling of response values from I2CReadByte - could return < 0 error values.
2024-03-22 A bit more explicit handling for handling ENGLISH and DEFAULT locale.
2024-03-25 [IMP] firmware: Application E8x Telephone audio fix * Drop TCU overlay on E8x vehicles with Navigation so that the radio will accept the volume changes
2024-03-26 [FIX] firmware: Application Static Code Analysis Cleanup
    * Buffer overflows
    * Abundant volatile declarations
    * Re-declaration of volume in branches
    * Small cleanups
    * Unnecessary casts
    * Wrong operator when handling EEprom, preventing access to more that first 256 bytes
2024-03-27 [IMP] firmware: Application Lint * Minor tweaks to improve readability
2024-04-01 [IMP] firmware: Application Lint & Refactor for Nav Datetime * Move GPS time handling code into handler_ibus.c * Remove DST / Timezone auto-setting code as it cannot possibly know what offset the veh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
2024-09-11 [FIX] Redraw display after coming from navigation display properly.
2024-10-27 Track CarPlay display state and handle CDC command next/prev only when not in CarPlay.
2024-10-27 CleanUp
2024-10-30 [IMP] firmware: Application - Translate Voice Assistant to DE
2025-01-15 Add missing init for time handling used for time-zone setup.
2025-02-02 [IMP] Rename display mode REVERSE_CAM to EXTERNAL to better reflect potential use
2025-04-06 [IMP] application: Add Analog Call mode * Allows users to make use of the analog audio path for calls to avoid the lack of clarity with TCU audio mode
2025-04-06 [IMP] application: Fix CD53 metadata display on V1 units * Correctly assertain if metadata is fresh to keep it from updating constantly
2025-05-02 Use IBUS packet indices in more places
2025-05-13 [FIX] application: Fix ZKE identification off-by-one bug
2025-05-13 [IMP] Handle CarPhonics CarPlay switching and Config menu to set default
2025-05-13 [IMP] Handle TONE button to switch out of CarPlay screen [IMP] On Calls and Siri switch to CarPlay screen [FIX] Improve state tracking for display switching [FIX] Improve screen data init after switc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
2025-05-14 [FIX] Reuse emptied Timer Task Slots to prevent task exhaustion when reversing often
2026-02-04 [IMP] firmware: SCREAMING_SNAKE_CASE FOREVER
2026-02-04 [IMP] firmware: Bootloader -- Minor update
2026-02-05 [IMP] firmware: Application: Static code analysis & readability improvements * Initialize all char arrays to zero * Subscript arrays with defined values rather than magic numbers * Remove i2c.c usele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
2026-02-05 [IMP] firmware: Application: Minor readability updates
2026-02-06 [IMP] firmware: Application: Carphonics Module Support * Implement control functionality for the Carphonics module * Add in handling of the screen state when the Carphonics module is active, or any o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
2026-02-06 [IMP] firmware: Application: Minor ZKE build fixes
2026-02-09 [IMP] firmware: Remove unused symbols
2026-02-10 [IMP] firmware: Application: Single Line UI Enhancements * Remove OBC Active State in favor of a UI state, so we can further pair down the CD53 and MID implementations
2026-02-13 [FIX] firmware: Application: BM83/BC127 device connection fixes * Fix bugs with hung connections on the BM83 * Centralized logic for connections so that we are not trying to connect to multiple devic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
2026-02-17 [IMP] firmware: Application 1.4.3 Improvements * Refactor volume loweing functionality to lower the vehicle volume rather than A2DP volume * Fix Low Range Navigate to Gas Station functionality * Forc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
2026-02-20 [IMP] firmware: Application 1.4.5: TEL functions * Implement all of the relevant TEL functions for the GT (and others)
2026-02-23 [IMP] firmware: Application 1.4.6: BC127 PBAP * Implement PBAP functions * Implement PBAP Parsing * Increase char queue size 128 bytes to 768 out of an abundance of caution * Implement data streaming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
2026-02-27 [IMP] firmware: Application 1.4.8 / BMBT Telephony * Implementation of the telephone menus with PBAP * Implement the dial pad, directory, Top-8 and Last Dialed
2026-03-02 [IMP] firmware: Application 1.4.11: PDC & PBAP fixes * Refactor PDC handling: replace IBusPDCSensorStatus_t / pdcSensors with unified IBUSPDCStatus_t / pdc struct that includes active/inactive status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
2026-03-03 [IMP] firmware: Application: PDC / Reversing fixes * Resolve issues with lowering volume on reverse * Resolve issues with PDC handling
2026-03-05 [FIX] firmware: Inspect, Reset and Log RCON register * Track the RCON register so we have a better idea when the MCU resets for an unexpected reason * Add RCON reason to "GET ERR" output
2026-03-07 [IMP] firmware: Application: PDC Improvements * Set the poll rate to 750ms to prevent issues with updates causing the high OBC to "flicker" * Fix logic for identifying updated PDC data * Add a catch 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
2026-03-09 [IMP] firmware: Application BMBT UI Fixes * Force a screen rewrite when the raido clears out the buffers for the view mode we are currently using
2026-03-10 [IMP] firmware: Application Bugfixes * BC127: Remove useless cidLen * IBus: * Fix bug where the entire tx slot is not cleaned between frame * Fix usage of uint8_t to hold a uint32_t * Remove extra sp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
2026-03-17 [IMP] firmware: Application Temperature Fixes & 1.4.26 * Refactor temperature updates * Remove a bunch of magic numbers * Free up a lot of logic in the sensor update handler for bmbt.c
2026-03-19 [IMP] firmware: Locale Improvements * Used an LLM to at least fix up some of the translations. Hopefully it did not hallucinate too hard, but it did admit its Estonian was bad.
2026-03-20 [FIX] firmware: Application Menu Selection Issues * Apparently the GT does not reliably send the menu select release event, which causes issues. We now use a timer to artificially inject that release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

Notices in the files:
parts and their libraries:
SparkFun-Aesthetics: Licensing: Creative Commons ShareAlike 4.0 International - https://creativecommons.org/licenses/by-sa/4.0
SparkFun-Aesthetics: Released under the Creative Commons Attribution Share-Alike 4.0 License
SparkFun-Aesthetics: https://creativecommons.org/licenses/by-sa/4.0
